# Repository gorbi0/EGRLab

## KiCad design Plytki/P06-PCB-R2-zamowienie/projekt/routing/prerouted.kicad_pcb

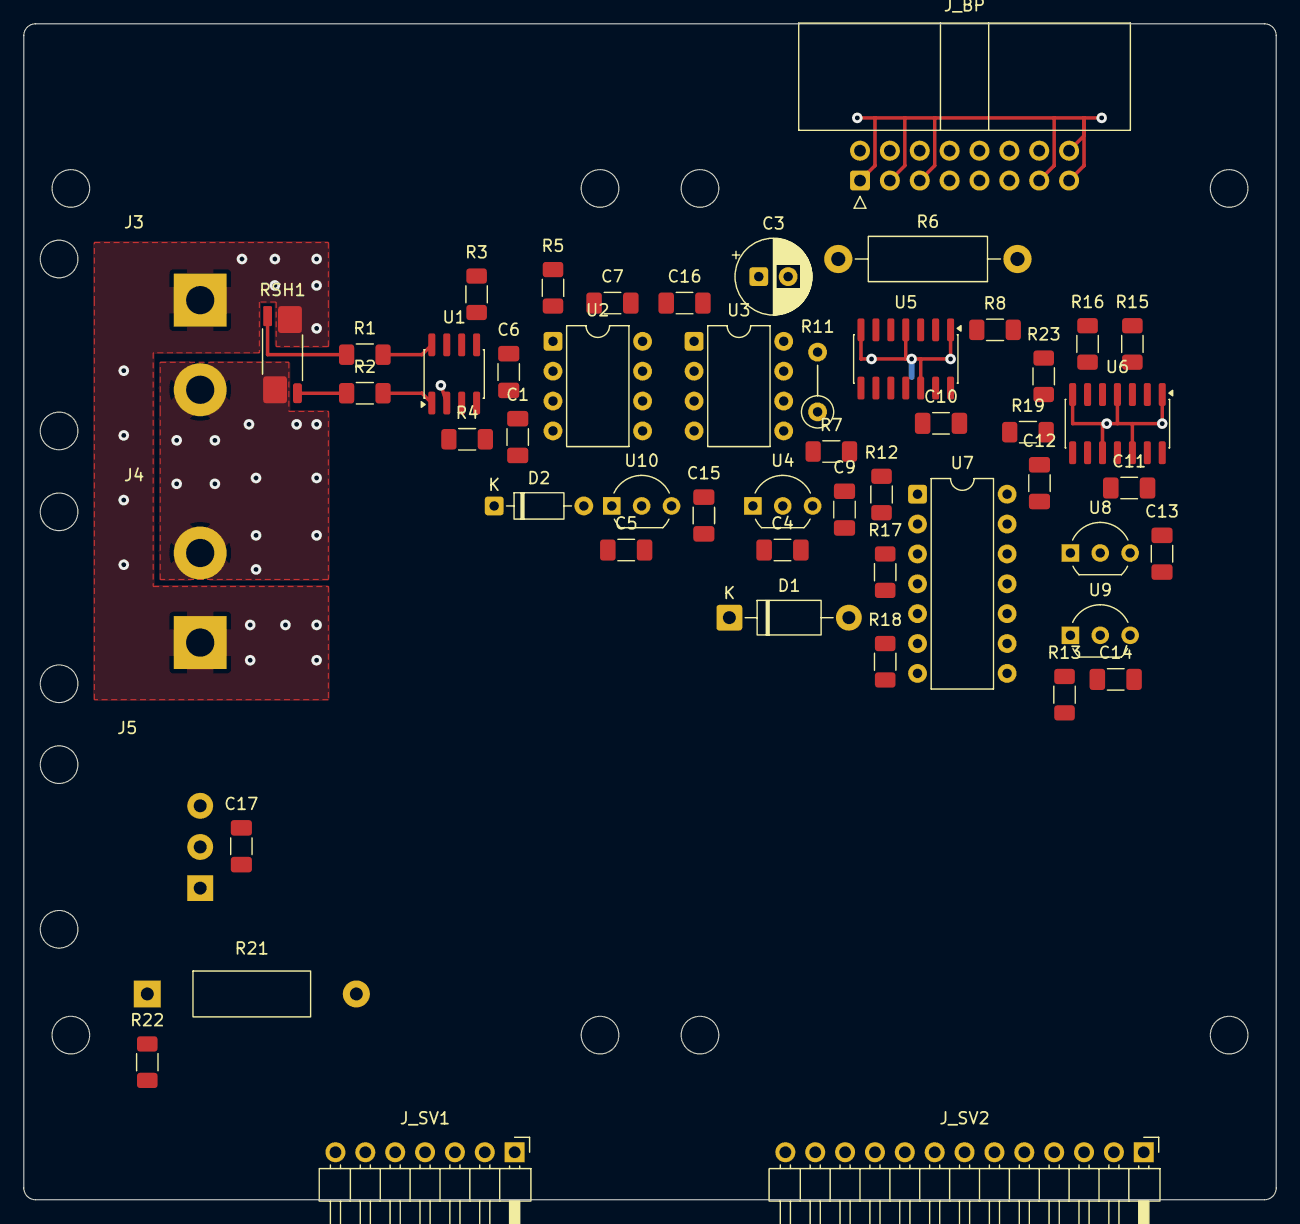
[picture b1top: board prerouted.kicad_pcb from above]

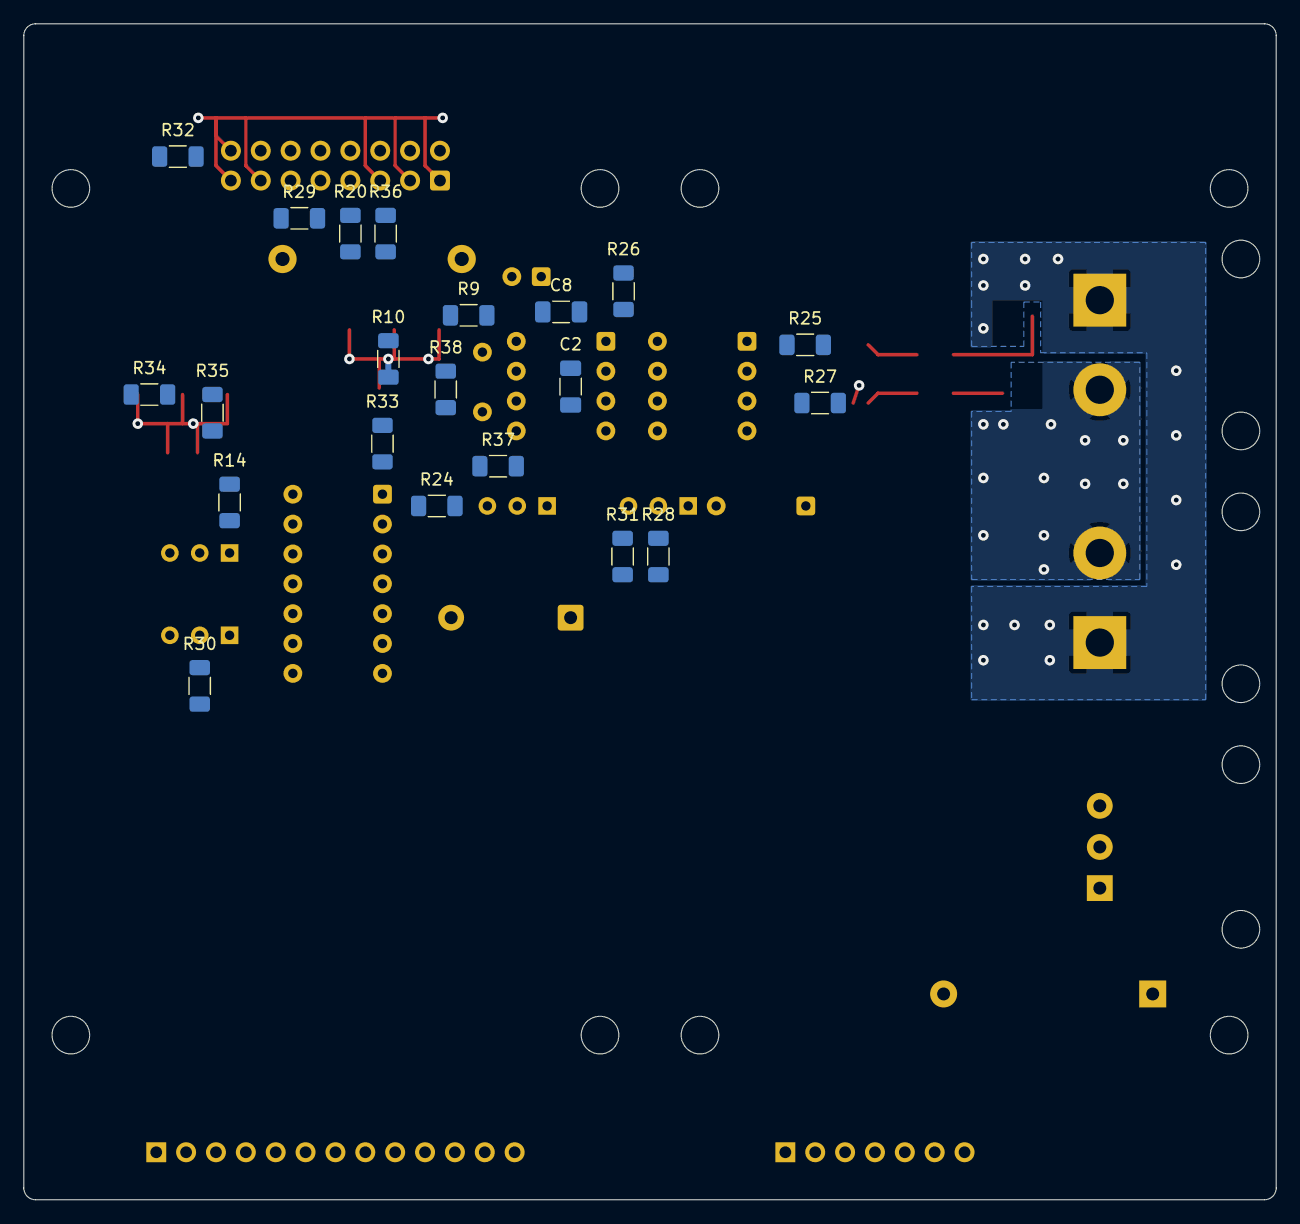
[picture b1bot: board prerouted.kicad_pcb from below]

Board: 2 copper layers, 106.5 x 100.0 mm, 82 parts (21 on the bottom side), 48 nets.

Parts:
C1: 470n; C_1206_3216Metric_Pad1.33x1.80mm_HandSolder
C2: 470p; C_1206_3216Metric_Pad1.33x1.80mm_HandSolder
C3: 220u; CP_Radial_D6.3mm_P2.50mm
C4, C5: 4.7u; C_1206_3216Metric_Pad1.33x1.80mm_HandSolder
C6, C7, C8, C9, C10, C11, C12, C13, C14, C15, C16, C17: 100n; C_1206_3216Metric_Pad1.33x1.80mm_HandSolder
D1: 1N5819; D_DO-41_SOD81_P10.16mm_Horizontal
D2: BAT85; D_DO-35_SOD27_P7.62mm_Horizontal
H1, H2, H3, H4, H5, H6, H7, H8: M3 NPTH
J3: ISERIES; PTH_ISERIES
J4: SW1 A; PTH_BYPASS
J5: SW1 B; PTH_SWSTATUS
J_BP: J_BP; IDC-Header_2x08_P2.54mm_Horizontal
J_SV1: J_SV1 SERWIS 1x7; PinHeader_1x07_P2.54mm_Horizontal
J_SV2: J_SV2 SERWIS 1x13; PinHeader_1x13_P2.54mm_Horizontal
R1, R2: 10R; R_1206_3216Metric_Pad1.30x1.75mm_HandSolder
R3, R4: 5.11K; R_1206_3216Metric_Pad1.30x1.75mm_HandSolder
R5, R12: 47R; R_1206_3216Metric_Pad1.30x1.75mm_HandSolder
R6: 1R; R_Axial_DIN0411_L9.9mm_D3.6mm_P15.24mm_Horizontal
R7, R9, R13, R14, R15, R16, R17, R18, R20, R25, R26, R27, R28, R33, R34: 10K; R_1206_3216Metric_Pad1.30x1.75mm_HandSolder
R8, R10, R23: 100K; R_1206_3216Metric_Pad1.30x1.75mm_HandSolder
R11: 47K; R_Axial_DIN0207_L6.3mm_D2.5mm_P5.08mm_Vertical
R19: 100R; R_1206_3216Metric_Pad1.30x1.75mm_HandSolder
R21: 39R; R_PR02_P17.78
R22, R24, R29, R30, R31, R32, R35, R36, R37, R38: 1K; R_1206_3216Metric_Pad1.30x1.75mm_HandSolder
RSH1: 5m; R_Shunt_Vishay_WSK2512_T1.19mm_SenseE1.70
U1: INA240A2; SOIC-8_3.9x4.9mm_P1.27mm
U2: MCP6022-I/P; DIP-8_W7.62mm
U3: MCP3201-BI/P; DIP-8_W7.62mm
U4: MCP1702-3302E/TO; TO-92_Inline_Wide
U5, U6: 74LVC125AD; SOIC-14_3.9x8.7mm_P1.27mm
U7: SN74HC08N; DIP-14_W7.62mm
U8: MCP120-300DI/TO; TO-92_Inline_Wide
U9: MCP120-450DI/TO; TO-92_Inline_Wide
U10: MCP1525-I/TO; TO-92_Inline_Wide

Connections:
3V3_IO: J_BP.14, R32.1
3V3_P06: C4.1, C7.1, C8.1, C10.1, C11.1, C12.1, C13.1, C15.1, D1.2, D2.1, R7.1, R8.1, R11.1, R14.1, R24.1, R31.1, U2.8, U3.8, U4.3, U5.13, U5.14, U6.13, U6.14, U7.14, U8.2, U10.3
5VA_P06: C3.1, C6.1, C9.1, C14.1, C17.1, D1.1, J5.1, R6.2, R13.1, R30.1, U1.6, U4.2, U9.2
5V_SYS: J_BP.10, J_BP.12, R6.1, R29.1
/ANA/INA_MINUS: R2.2, U1.1
/ANA/INA_PLUS: R1.2, U1.8
/ANA/I_DIV: C1.1, R3.2, R4.1, U2.3
/DIG/ADC_DOUT: R11.2, U3.6, U5.9
/DIG/DOUT_TX: R12.1, U5.8
/FORCE/ECU_P1: J3.1, J4.1, RSH1.1
/FORCE/EGR_P1: J3.2, J4.2, RSH1.4
/READY/LOGGER_OK_LOCAL: R18.1, U6.9, U7.6
/READY/LOGGER_OK_TX: R19.1, U6.8
/READY/RAILS_OK: R17.1, U7.3, U7.4
/READY/SUP5_RAW: R13.2, U6.2, U9.1
/READY/SW_SENSE: R22.2, R23.1, U6.5
/SERWIS/SRV_3V3_IO: J_SV2.6, R32.2
/SERWIS/SRV_3V3_P06: J_SV2.4, R31.2
/SERWIS/SRV_5VA_P06: J_SV2.3, R30.2
/SERWIS/SRV_5V_SYS: J_SV2.2, R29.2
/SERWIS/SRV_ADC_AIN: J_SV1.3, R26.2
/SERWIS/SRV_CLK_LOCAL: J_SV2.12, R38.2
/SERWIS/SRV_CS_LOCAL_N: J_SV2.11, R37.2
/SERWIS/SRV_I_L_OUT: J_SV1.2, R25.2
/SERWIS/SRV_LOGGER_CURRENT_OK: J_SV2.10, R36.2
/SERWIS/SRV_REF25: J_SV1.6, R28.2
/SERWIS/SRV_REF_BUF: J_SV1.5, R27.2
/SERWIS/SRV_SHUNT_ENABLED: J_SV2.9, R35.2
/SERWIS/SRV_SUP3_N: J_SV2.7, R33.2
/SERWIS/SRV_SUP5_N: J_SV2.8, R34.2
ADC_AIN: C2.1, R5.2, R26.1, U3.2
ADC_BUF: R5.1, U2.1, U2.2
ADC_DOUTA: J_BP.4, R12.2
ADC_SCLK: J_BP.2, R10.1, U5.5
CLK_LOCAL: R9.1, R38.1, U3.7, U5.6
CS_ILOG_N: J_BP.6, R8.2, U5.2
CS_LOCAL_N: R7.2, R37.1, U3.5, U5.3, U5.10
GND: C1.2, C2.2, C3.2, C4.2, C5.2, C6.2, C7.2, C8.2, C9.2, C10.2, C11.2, C12.2, C13.2, C14.2, C15.2, C16.2, C17.2, J5.3, J_BP.1, J_BP.3, J_BP.5, J_BP.7, J_BP.9, J_BP.11, J_BP.13, J_BP.15, J_BP.16, J_SV1.1, J_SV1.4, J_SV1.7, J_SV2.1, J_SV2.5, J_SV2.13, R4.2, R9.2, R10.2, R15.2, R16.2, R17.2, R18.2, R20.2, R21.2, R23.2, R24.2, U1.2, U2.4, U3.3, U3.4, U4.1, U5.1, U5.4, U5.7, U5.12, U6.1, U6.4, U6.7, U6.10, U6.12, U7.7, U7.9, U7.10, U7.12, U7.13, U8.3, U9.3, U10.1
I_L_OUT: R3.1, R25.1, U1.5
K_MINUS: R2.1, RSH1.3
K_PLUS: R1.1, RSH1.2
LOGGER_CURRENT_OK: J_BP.8, R19.2, R20.1, R36.1
REF25: C5.1, C16.1, D2.2, R28.1, U2.5, U3.1, U10.2
REF_BUF: R27.1, U1.3, U1.7, U2.6, U2.7
SHUNT_ENABLED: R16.1, R35.1, U6.6, U7.5
SUP3_N: R14.2, R33.1, U7.1, U8.1
SUP5_N: R15.1, R34.1, U6.3, U7.2
SW_RAW: J5.2, R21.1, R22.1

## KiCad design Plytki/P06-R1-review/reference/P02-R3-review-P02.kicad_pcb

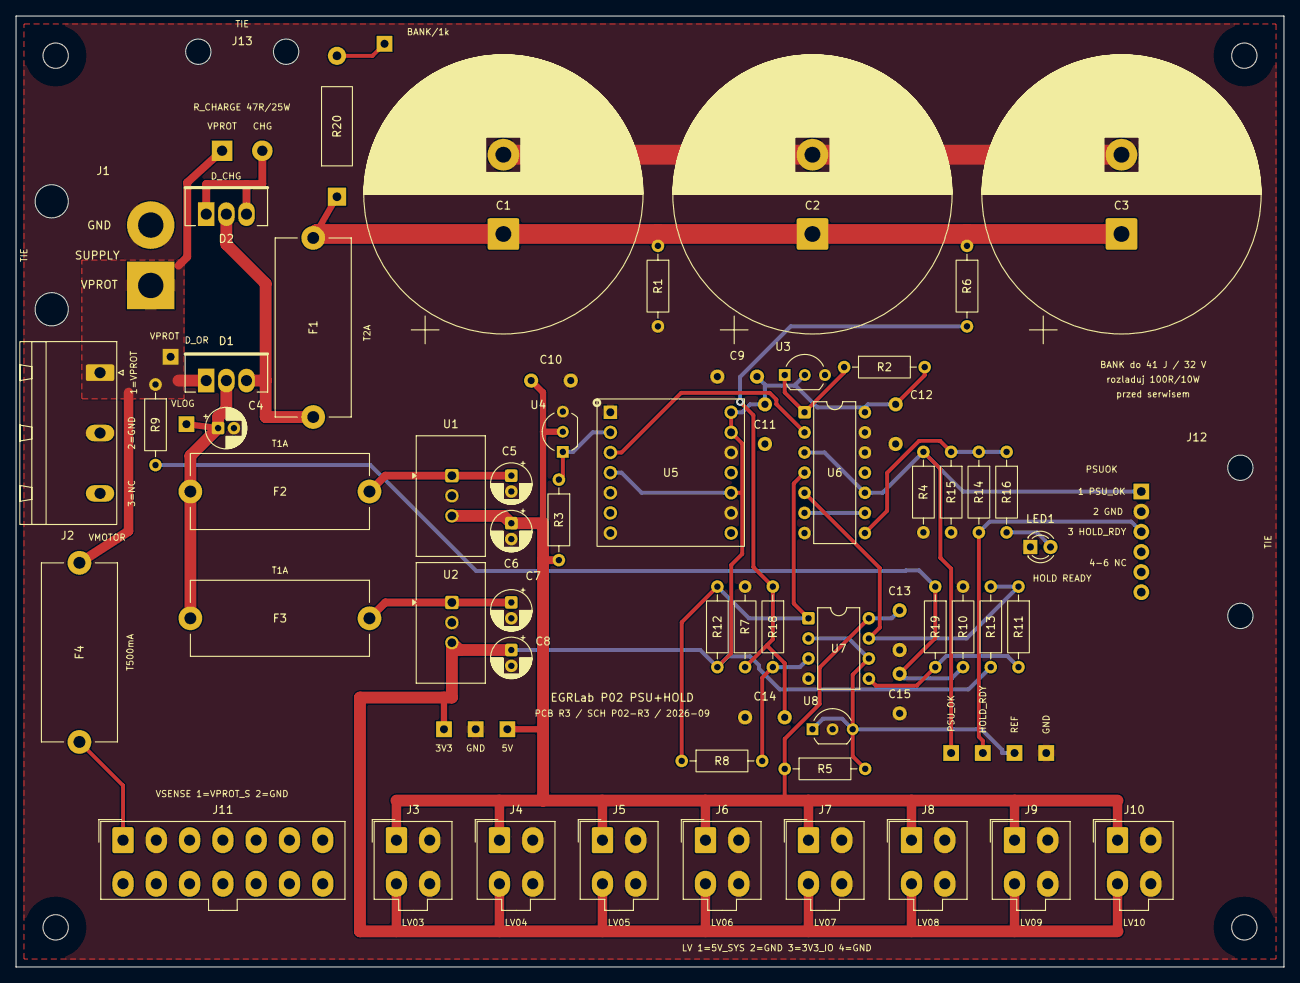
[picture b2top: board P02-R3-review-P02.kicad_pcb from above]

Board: 2 copper layers, 160.0 x 120.0 mm, 76 parts (0 on the bottom side), 27 nets.

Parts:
C1, C2, C3: 22000u; CP_Radial_D35.0mm_P10.00mm_SnapIn
C4, C6, C8: 22u; CP_Radial_D5.0mm_P2.00mm
C5, C7: 10u; CP_Radial_D5.0mm_P2.00mm
C9, C10, C11, C12, C13: 100nF; C_Vishay_K15_H5_P5
C14, C15: 10nF; C_Vishay_K15_H5_P5
D1, D2: STPS20100CT; TO220_3_P2.54_Drill1.4
F1: T2A; Fuseholder_Cylinder-5x20mm_Stelvio-Kontek_PTF78_Horizontal_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
F2, F3: T1A; Fuseholder_Cylinder-5x20mm_Stelvio-Kontek_PTF78_Horizontal_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
F4: T500mA; Fuseholder_Cylinder-5x20mm_Stelvio-Kontek_PTF78_Horizontal_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
H1, H2, H3, H4: M3 NPTH
J1: SUPPLY; Pigtail_PWR_2x2.5mm2
J2: VMOTOR; PhoenixContact_GMSTBA_2,5_3-G-7,62_1x03_P7.62mm_Horizontal
J3: LV03; Molex_Mini-Fit_Jr_5566-04A_2x02_P4.20mm_Vertical
J4: LV04; Molex_Mini-Fit_Jr_5566-04A_2x02_P4.20mm_Vertical
J5: LV05; Molex_Mini-Fit_Jr_5566-04A_2x02_P4.20mm_Vertical
J6: LV06; Molex_Mini-Fit_Jr_5566-04A_2x02_P4.20mm_Vertical
J7: LV07; Molex_Mini-Fit_Jr_5566-04A_2x02_P4.20mm_Vertical
J8: LV08; Molex_Mini-Fit_Jr_5566-04A_2x02_P4.20mm_Vertical
J9: LV09; Molex_Mini-Fit_Jr_5566-04A_2x02_P4.20mm_Vertical
J10: LV10; Molex_Mini-Fit_Jr_5566-04A_2x02_P4.20mm_Vertical
J11: VSENSE; Molex_Mini-Fit_Jr_5566-14A_2x07_P4.20mm_Vertical
J12: PSUOK; Pigtail_PSUOK_6x_P2.54
J13: R_CHARGE; Pigtail_RCHARGE_2xAWG20
LED1: GREEN 3mm; LED_D3.0mm
R1: 4K7; R_Axial_DIN0207_L6.3mm_D2.5mm_P10.16mm_Horizontal
R2, R3, R4, R7, R10, R12, R13, R15, R18, R19: 10K; R_Axial_DIN0207_L6.3mm_D2.5mm_P10.16mm_Horizontal
R5: 330R; R_Axial_DIN0207_L6.3mm_D2.5mm_P10.16mm_Horizontal
R6: 30K1; R_Axial_DIN0207_L6.3mm_D2.5mm_P10.16mm_Horizontal
R8, R11: 1M; R_Axial_DIN0207_L6.3mm_D2.5mm_P10.16mm_Horizontal
R9: 38K3; R_Axial_DIN0207_L6.3mm_D2.5mm_P10.16mm_Horizontal
R14: 1K; R_Axial_DIN0207_L6.3mm_D2.5mm_P10.16mm_Horizontal
R16: 470R; R_Axial_DIN0207_L6.3mm_D2.5mm_P10.16mm_Horizontal
R20: 1K; R_PR02_P17.78
TP1, TP2, TP3, TP4, TP5, TP6, TP7, TP8, TP9, TP10: TestPad_1
U1: TSR 2-2450; Converter_DCDC_TRACO_TSR2-xxxx_THT
U2: TSR 2-2433; Converter_DCDC_TRACO_TSR2-xxxx_THT
U3: MCP120-300DI/TO; TO-92_Inline_Wide
U4: MCP120-450DI/TO; TO-92_Inline_Wide
U5: 74LVC125A; Adapter_SO14_DIP14_W15.24_Kamami575068
U6: SN74HC08N; DIP-14_W7.62mm
U7: LM2903P; DIP-8_W7.62mm
U8: TL431BILP; TO-92_Inline_Wide

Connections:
3V3_IO: C8.1, C9.1, C11.1, C12.1, J3.3, J4.3, J5.3, J6.3, J7.3, J8.3, J9.3, J10.3, R2.2, R12.2, R13.2, TP5.1, U2.3, U3.2, U5.4, U5.10, U5.13, U5.14, U6.14
5V_SYS: C6.1, C10.1, C13.1, J3.1, J4.1, J5.1, J6.1, J7.1, J8.1, J9.1, J10.1, R3.2, R5.1, TP4.1, U1.3, U4.2, U7.8
/CHARGE_D: D2.1, D2.3, J13.2
/HOLD/P02_BANK_CMP: R8.2, R18.2, U7.3
/HOLD/P02_BANK_DIV: C14.1, R6.2, R7.1, R18.1
/HOLD/P02_REF25: R5.2, TP9.1, U7.2, U7.6, U8.1, U8.3
/HOLD/P02_VPROT_CMP: R11.2, R19.2, U7.5
/HOLD/P02_VPROT_DIV: C15.1, R9.2, R10.1, R19.1
/HOLD_FUSED: D1.3, D2.2, F1.1
/HOLD_TP: R20.2, TP3.1
/LV/P02_VIN_DC5: C5.1, F2.2, U1.1
/LV/P02_VIN_DC33: C7.1, F3.2, U2.1
/MON/HOLD_READY: J12.3, R14.2, TP8.1
/MON/P02_HOLD_QUAL: U6.6, U6.9
/MON/P02_HOLD_READY_INT: R14.1, R15.1, R16.1, U6.8
/MON/P02_LED_A: LED1.2, R16.2
/MON/P02_SUP3_N: R2.1, U3.1, U6.1
/MON/P02_SUP5_N: U5.3, U6.2
/MON/P02_SUP5_RAW: R3.1, U4.1, U5.2
/MON/PSU_OK: J12.1, R4.1, TP7.1, U6.3, U6.10
/VPROT_SENSE: F4.2, J11.1
GND: C1.2, C2.2, C3.2, C4.2, C5.2, C6.2, C7.2, C8.2, C9.2, C10.2, C11.2, C12.2, C13.2, C14.2, C15.2, J1.2, J2.2, J3.2, J3.4, J4.2, J4.4, J5.2, J5.4, J6.2, J6.4, J7.2, J7.4, J8.2, J8.4, J9.2, J9.4, J10.2, J10.4, J11.2, J12.2, LED1.1, R1.2, R4.2, R7.2, R10.2, R15.2, TP6.1, TP10.1, U1.2, U2.2, U3.3, U4.3, U5.1, U5.5, U5.7, U5.9, U5.12, U6.7, U6.12, U6.13, U7.4, U8.2
HOLD_STORE: C1.1, C2.1, C3.1, F1.2, R1.1, R6.1, R20.1
P02_BANK_OK: R8.1, R12.1, U6.4, U7.1
P02_VPROT_OK: R11.1, R13.1, U6.5, U7.7
VLOG_RES: C4.1, D1.2, F2.1, F3.1, TP2.1
VPROT: D1.1, F4.1, J1.1, J2.1, J13.1, R9.1, TP1.1
